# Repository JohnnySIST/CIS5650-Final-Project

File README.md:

# CIS5650-Final-Project : Walk on Stars for Interactive PCB Simulation

# Overview

[LIVE DEMO](https://johnnysist.github.io/CIS5650-Final-Project/)

We are team **Circuit Nova** : [Oliver Hendrych](https://github.com/hendrych-upenn), [Lewis Ghrist](https://siwel-cg.github.io/siwel.cg_websiteV1/index.html#home), and [Hongyi Ding](https://johnnyding.com/portfolio). This project is a browser-based, WebGPU thermal simulation tool for PCB design and prototyping, built on the Walk on Stars (WoStr) algorithm. Users can import or draw PCB layouts, set boundary condition types and values, and interactively move components while the heat distribution updates in real time.

# Motivation and Background

Modern electronics are limited by heat dissipation. Being able to quickly visualize and simulate heat diffusion on PCBs is critical during early prototyping, yet most PCB design tools provide little to no thermal feedback while adjusting layouts. Full finite-element solvers are accurate but slow and don't allow for layout adjustments. Doing a global, high-fidelity solve is also often overkill and requires a full re-simulation every time a small change is made. This project targets that bottleneck by introducing a browser-based GPU thermal estimator built on the Walk-on-Stars (WoStr) algorithm. WoStr allows for fast re-simulation on geometry changes, localized solves over targeted regions, and a progressive convergence that provides immediate, intermediate estimates. All of these are advantageous for quick design iteration and prototyping.

## Current Open Source Availability

Current open source options are limited and take a large number of processing steps before achieving a final result [1]. Users are forced to download many distinct pieces of software for each part of the process, beyond the initial KiCad development, if they want to continue license-free [2]. KiCad boards are exported first to Salome to perform mesh building and conversion. Then, that output is exported ElmerVTK where the FEM simulation is run. Finally, to produce high quality images, that output must be exported to Paraview. If one wants to iterate on their design, then go back to KiCad, modify the appropriate geometry, then complete this whole process again. In our software, the last 3 steps will be condensed to a single software, which will also allow for interative editing to shorten the design loop

## Walk on Spheres & Walk on Stars

Walk on Spheres works by launching random walks from query points until they hit a boundary. Drawing inspiration from path tracing and sphere tracing, each walk contributes to a Monte Carlo estimator that converges toward the true solution of the steady-state heat equation. Because each walk is independent, the method is embarrassingly parallel, making it a perfect fit for WebGPU compute shaders.

Walk on Stars is an extension to the WoS algorithm to allow for a combination of Dirichlet and Neumann boundary conditions, a feature that is needed for physically based heat simulations. The structure is the same in that it is a Monte Carlo based method using random walks from a set of query points. The radius of the sphere used for sphere tracing is only dependent on the Dirichlet boundaries. When walking to the uniformly sampled point on this sphere, if we cross a Neumann boundary, we reflect our walk about the boundary's flux direction and adjust values based on that flux. The walks continue on, only terminating when we finally hit a Dirichlet boundary. This allows for accurate sinks and sources. Again we can take advantage of GPU parallelization to make this process extremely fast.

The original papers, as well as many extentions, can be found here: [https://rohan-sawhney.github.io/mcgp-resources/](https://rohan-sawhney.github.io/mcgp-resources/)

| Walk on Spheres (Dirichlet only)  | Walk on Stars (Dirichlet + Neumann) |
| :-------------------------------: | :---------------------------------: |
|  |    |

# Break Down

The general pipeline involves two main compute shaders. First, we do an initial screening of our simulation domain to get just the query points within the boundaries of our geometry. This can be done once before the simulation starts and allows us to only simulate on point's that will actually result in meaning full data. These query points are then shipped to the second compute shader where the real work happens. This second compute shader handles the actuall simulation. For each query point, we send out these random walks, stepping based on the closest distance to a boundary. This closest distance is found using a BVH struture (or in this case BAH structure since we are in 2D), which drastically speeds up walk times, especially in complex boards. As explained in the WoStr method, at Neumann boundaries, this walk get reflected, picking up some flux value, and at Dirichlet boundarie's, the walk ends and returns the Dirichlet boundary value along with any accumulated flux along the walk. These results then get sent to a final fragment shader, which averages all the walk results for each query point, fits that value through a simple color ramp, and draws it to the screen along with the boundary geometry.

## Interactivity

Here is the layout of the UI:

Major features include:

- Import and export as KiCad PCB formats
- Simulation zone selection
- Change simulation resolution
- Geometry selection, addition/deletion and alteration
- Change boundary conditions and values
- Selection of board layers
- Zooming, panning camera controls
- Toggle simulation on/off
- Live FPS display

A unique advantage of this WoStr method, is that because it is based only on a set of initial query points, we don't need to do a global solve to get results. To take advantage of this, we implemented a simulation zone selection feature that lets users focus computation on a specific region of interest. For complex boards, or if there is a specific area you are particularly interested in, you can easily simulate just on that area in a higher resolution, without paying for the cost of simulating the entire board.

The main user interaction feature is being able to select, add/delete, and move geometry as well as change the boundary types and values as needed. This allows for custom board creation or user imported boards to be edited and adjusted. The final configuration can then be exported out.

The user can also choose which layer of the board they would like to modify and simulate. Modern PCB designs contain many layers, and it is important to be able to simulate any of them. Below is an example of this with the KiCad `kit-dev-coldfire-xilinx_5213` demo project:

|                 FCu Layer                  |                  In1Cu Layer                   |                  In2Cu Layer                   |
| :----------------------------------------: | :--------------------------------------------: | :--------------------------------------------: |
|  |  |  |

Finally, for some quality of life features, we implemented a basic camera system for navigating the board, a live FPS display for performance monitoring, a pause button for the simulation, and a selection menu for adjusting simulation resolution.

Here is a demo video of the tool in action.

## KiCad Integration

An important part of open source development is integrating with other tools from the ecosystem. KiCad is a very popular open source EDA (electronic design automation) tool that is used for PCB design and prototyping. Additionally, other software have capabilities to import and export KiCad PCB files, making it a common element for PCB design. As such, we chose it as our primary integration point, for both import and export of board geometry. Our tool uses a [forked](https://github.com/hendrych-upenn/kicadts) version of the [kicadts](https://github.com/tscircuit/kicadts) package to parse `.kicad_pcb` files and reexport the modified `.kicad_pcb` file. Its plaintext format makes it easy to parse and modify. Upon importing a KiCad PCB file, the tool will parse the file and extract the footprint and segment geometries, which can then be used in the simulation. The user can then modify, delete, or add geometry as needed. When the user is done, the geometry can be exported back to a KiCad PCB file.

# Future Work

There are still some additional features that can be added for more functionality or better resutls. For starters, there has been a lot of recent work on extending or improving the Walk on Stars algorithm. This includes things like faster convergence and more complex boundary types. The simulation at the moment doesn't take into account material properties, which in a full, physically accurate simulation is important. As a prototying tool, getting this approximate solution is still valuable, but WoStr can be extended to support materal properties. Additionally, the pipeline can be extended to support more geometry types beyond simple segments and circles, making it more in line with prexisting PCB editors. Finally, as always, further optimizations and performance improvemnts can be made for smoother and faster results.

# References

1: [https://jrainimo.com/build/2024/11/oss-thermal-simulation-of-pcbs/](https://jrainimo.com/build/2024/11/oss-thermal-simulation-of-pcbs/)

2: [https://resources.altium.com/p/why-you-should-use-thermal-prototyping-instead-simulations](https://resources.altium.com/p/why-you-should-use-thermal-prototyping-instead-simulations)

3: [https://jacco.ompf2.com/2022/04/13/how-to-build-a-bvh-part-1-basics/](https://jacco.ompf2.com/2022/04/13/how-to-build-a-bvh-part-1-basics/)

4: [https://rohan-sawhney.github.io/mcgp-resources/](https://rohan-sawhney.github.io/mcgp-resources/)

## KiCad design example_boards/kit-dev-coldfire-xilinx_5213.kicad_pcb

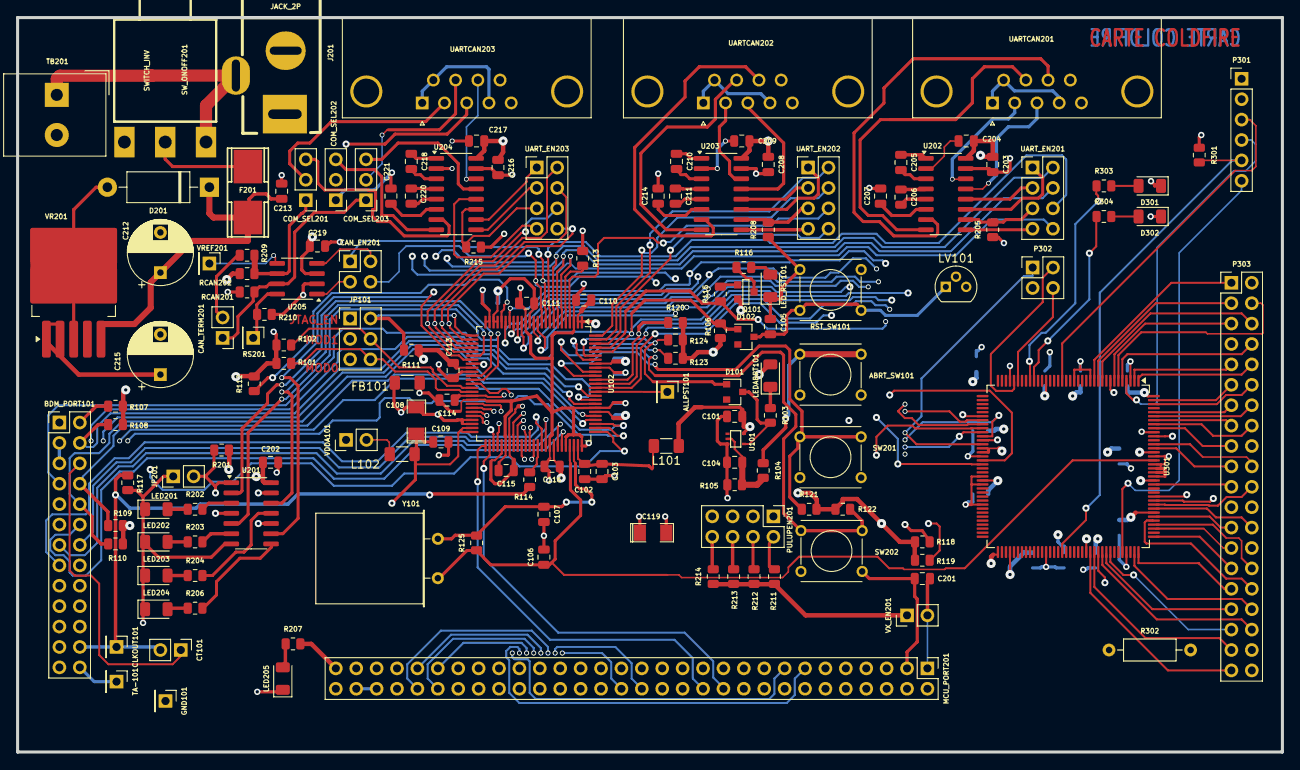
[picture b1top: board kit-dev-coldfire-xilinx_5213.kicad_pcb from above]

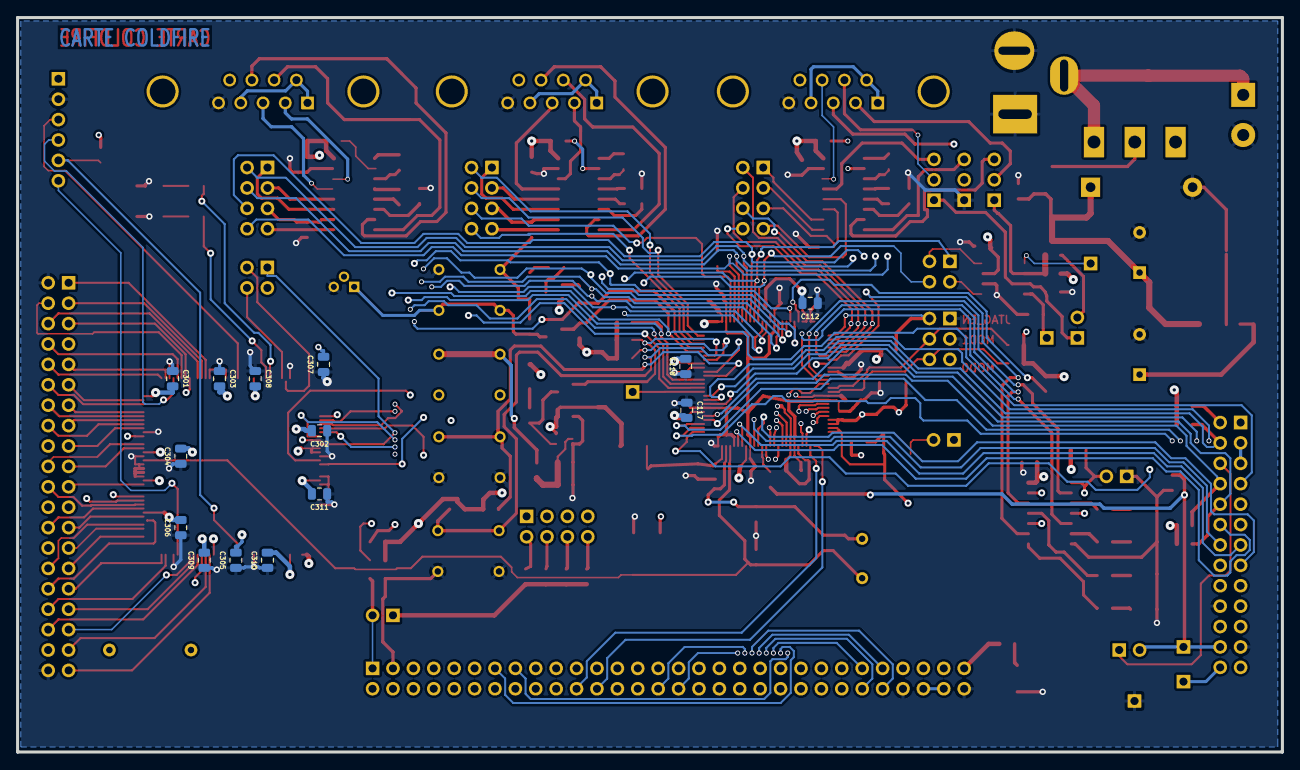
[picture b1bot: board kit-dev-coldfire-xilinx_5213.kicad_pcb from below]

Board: 4 copper layers, 157.5 x 91.4 mm, 160 parts (14 on the bottom side), 209 nets.

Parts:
ABRT_SW101: SW_PUSH; SW_PUSH_SMALL
ALLPST101: CONN_1; PinHeader_1x01_P2.54mm_Vertical
BDM_PORT101: CONN_13X2; PinHeader_2x13_P2.54mm_Vertical
C101, C103, C104, C109, C110, C111, C112, C113, C114, C115, C116, C117, C118, C201, C202, C203, C204, C205, C206, C207, C208, C209, C210, C211, C213, C214, C216, C217, C218, C219, C220, C221, C301, C302, C303, C304, C305, C306, C307, C308, C309, C310, C311: 100nF; C_0805_2012Metric
C102, C105: 1nF; C_0805_2012Metric
C106, C107: 10pF; C_0805_2012Metric
C108: 10uF; SM1206POL
C119: 100uF; SM1206POL
C212: 10uF; CP_Radial_D8.0mm_P5.00mm
C215: 220uF; CP_Radial_D8.0mm_P5.00mm
CAN_EN201: CONN_2X2; PinHeader_2x02_P2.54mm_Vertical
CAN_TERM201: JUMPER; PinHeader_1x02_P2.54mm_Vertical
CLKOUT101: CONN_1; PinHeader_1x01_P2.54mm_Vertical
COM_SEL201, COM_SEL202, COM_SEL203: CONN_3; PinHeader_1x03_P2.54mm_Vertical
CT101: JUMPER; PinHeader_1x02_P2.54mm_Vertical
D101, D102: BAT54; D_SOT-23_ANK
D201: 1N4004; D_DO-15_P12.70mm_Horizontal
D301, D302: LED; LED_1206_3216Metric
F201: FUSE; FSUPCMS
FB101: BEAD; R_1206_3216Metric_Pad1.30x1.75mm_HandSolder
GND101: CONN_1; PinHeader_1x01_P2.54mm_Vertical
J201: JACK_2P; JACK_ALIM
JP101: JUMPER_TRIPLE; PinHeader_2x03_P2.54mm_Vertical
JP201: JUMPER; PinHeader_1x02_P2.54mm_Vertical
L101, L102: 10uH; R_1206_3216Metric_Pad1.30x1.75mm_HandSolder
LED201, LED202, LED203, LED204, LED205: LED; LED_1206_3216Metric
LEDABRT101: LED_RED; LED_1206_3216Metric
LED_RST101: LED_RED; LED_1206_3216Metric
LV101: DS1818; TO-92
MCU_PORT201: CONN_30X2; PinHeader_2x30_P2.54mm_Vertical
P301: CONN_6; PinHeader_1x06_P2.54mm_Vertical
P302: CONN_2X2; PinHeader_2x02_P2.54mm_Vertical
P303: CONN_20X2; PinHeader_2x20_P2.54mm_Vertical
PULUPEN201: CONN_4X2; PinHeader_2x04_P2.54mm_Vertical
Q101: 3906; SOT23EBC
R101, R102, R106, R107, R108, R109, R110, R111, R112, R211, R212, R213, R214: 4,7K; R_0805_2012Metric
R103, R116, R202, R203, R204, R206, R207: 270; R_0805_2012Metric
R104, R210, R303, R304: 1K; R_0805_2012Metric
R105: 20K; R_0805_2012Metric
R113: 0; R_0805_2012Metric
R114: 22; R_0805_2012Metric
R115: 4.7K; R_0805_2012Metric
R117, R118, R119, R120, R121, R122, R123, R124, R201, R205, R208, R215: 10K; R_0805_2012Metric
R125: 1M; R_0805_2012Metric
R209: 62; R_0805_2012Metric
R301: 4K7; R_0805_2012Metric
R302: 3,3; R_Axial_DIN0207_L6.3mm_D2.5mm_P10.16mm_Horizontal
RCAN201, RCAN202: R; R_0805_2012Metric
RS201: CONN_1; PinHeader_1x01_P2.54mm_Vertical
RST_SW101: SW_PUSH; SW_PUSH_SMALL
SW201, SW202: SW_PUSH; SW_PUSH_SMALL
SW_ONOFF201: SWITCH_INV; SW_SPDT
TA-101: CONN_1; PinHeader_1x01_P2.54mm_Vertical
TB201: CONN_2; Altech_AK300_1x02_P5.00mm_45-Degree
U101: 74AHC1G14; SOT353
U102: MCF5213-LQFP100; LQFP-100_14x14mm_P0.5mm
U201: 74HC125; SOIC-14_3.9x8.7mm_P1.27mm
U202, U203, U204: MAX202; SOIC-16_3.9x9.9mm_P1.27mm
U205: PCA82C251; SOIC-8_3.9x4.9mm_P1.27mm
U301: XCR3256-TQ144; TQFP-144_20x20mm_P0.5mm
UARTCAN201, UARTCAN202, UARTCAN203: DB9; DSUB-9_Female_Horizontal_P2.77x2.84mm_EdgePinOffset7.70mm_H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
UART_EN201, UART_EN202, UART_EN203: CONN_4X2; PinHeader_2x04_P2.54mm_Vertical
VDDA101: JUMPER; PinHeader_1x02_P2.54mm_Vertical
VR201: LT1129_QPACK; TO-263-5_TabPin3
VREF201: CONN_1; PinHeader_1x01_P2.54mm_Vertical
VX_EN201: JUMPER; PinHeader_1x02_P2.54mm_Vertical
Y101: 8MHz; Crystal_HC18-U_Horizontal

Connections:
+3.3V: ABRT_SW101.2, BDM_PORT101.9, BDM_PORT101.25 (P24), C101.2, C110.1, C111.1, C112.1, C113.1, C114.1, C115.1, C116.1, C117.1, C118.1, C119.1, C202.1, C203.1, C204.1, C208.1, C209.1, C215.1, C216.1, C217.1, C219.1, C301.1, C302.1, C303.1, C304.1, C305.1, C306.1, C307.1, C308.1, C309.1, C310.1, C311.1, L101.1, LEDABRT101.2 (A), LV101.2 (In), MCU_PORT201.59, P301.1, Q101.1 (E), R101.1, R102.1, R106.1, R107.1, R108.1, R109.1, R110.1, R111.1, R112.2, R118.2, R119.2, R120.2, R121.2, R122.2, R123.2, R124.2, R201.1, R207.2, R211.1, R212.1, R213.1, R214.1, R301.1, R302.1, RCAN202.1, U101.5 (VCC), U102.1 (VCC), U102.2 (VCC), U102.14 (VCC), U102.22 (VCC), U102.23 (VCC), U102.34 (VCC), U102.41 (VCC), U102.55 (VSTBY), U102.57 (VCC), U102.68 (VCC), U102.81 (VCC), U102.93 (VCC), U201.14 (VCC), U202.16 (VCC), U203.16 (VCC), U204.16 (VCC), U205.3 (VCC), U301.24 (VCC), U301.50 (VCC), U301.51 (VCC), U301.58 (VCC), U301.73 (VCC), U301.76 (VCC), U301.95 (VCC), U301.115 (VCC), U301.123 (VCC), U301.130 (VCC), U301.144 (VCC), VDDA101.1, VR201.1 (OUT), VR201.2 (SENSE), VX_EN201.1
/ALLPST: ALLPST101.1, U102.86 (ALLPST)
/AN0: MCU_PORT201.10, U102.43 (AN0/PAN0)
/AN1: MCU_PORT201.12, U102.44 (AN1/PAN1)
/AN2: MCU_PORT201.14, U102.45 (AN2/PAN2)
/AN3: MCU_PORT201.16, U102.46 (AN3/PAN3)
/AN4: MCU_PORT201.18, U102.54 (AN4/PAN4)
/AN5: MCU_PORT201.20, U102.53 (AN5/PAN5)
/AN6: MCU_PORT201.22, U102.52 (AN6/PAN6)
/AN7: MCU_PORT201.24, U102.51 (AN7/PAN7)
/BKPT-: BDM_PORT101.2, R107.2, U102.76 (~BKPT/TMS)
/CANRX: CAN_EN201.4, MCU_PORT201.28, PULUPEN201.7, U102.11 (SDA/CANRX/PAS1/URXD2)
/CANTX: CAN_EN201.1, MCU_PORT201.26, PULUPEN201.5, U102.10 (SCL/CANTX/PAS0/UTXD2)
/CLKIN/EXTAL: C107.1, R125.2, U102.73 (CLKIN/EXTAL), Y101.1
/CLKMOD0: JP101.6, R101.2, U102.40 (CLKMOD0)
/CLKMOD1: JP101.4, R102.2, U102.39 (CLKMOD1)
/DDAT0: BDM_PORT101.19, U102.77 (DDATA0/PDD4)
/DDAT1: BDM_PORT101.18, U102.78 (DDATA1/PDD5)
/DDAT2: BDM_PORT101.17, U102.83 (DDATA2/PDD6)
/DDAT3: BDM_PORT101.16, U102.84 (DDATA3/PDD7)
/DSCLK: BDM_PORT101.4, R108.2, U102.85 (DSCLK/~TRST)
/DSI: BDM_PORT101.8, R109.2, U102.79 (DSI/TDI)
/DSO: BDM_PORT101.10, R110.2, U102.80 (DSO/TDO)
/DSPI_DOUT: MCU_PORT201.17, U102.17 (QSPI_DOUT/EZPQ/CANTX/RXD0/PQS0), U301.47 (M12)
/DTIN0: MCU_PORT201.34, U102.36 (DTIN0/DTOUT0/PWM0/PTC0), U201.2 (D)
/DTIN1: MCU_PORT201.36, U102.37 (DTIN1/DTOUT1/PWM2/PTC1), U201.5 (D)
/DTIN2: MCU_PORT201.38, U102.31 (DTIN2/DTOUT2/PWM4/PTC2), U201.12 (D)
/DTIN3: MCU_PORT201.40, U102.32 (DTIN3/DTOUT3/PWM6/PTC3), U201.9 (D)
/GPT0: MCU_PORT201.49, U102.58 (GPT0/PWM1/PTA0)
/GPT1: MCU_PORT201.50, U102.59 (GPT1/PWM3/PTA1)
/GPT2: MCU_PORT201.51, U102.61 (GPT2PWM5//PTA2)
/GPT3: MCU_PORT201.52, U102.62 (GPT3/PWM7/PTA3)
/IRQ-1: MCU_PORT201.2, R118.1, U102.87 (~IRQ1/PNQ1/SYNCA/PWM1), U301.42 (O2)
/IRQ-2: MCU_PORT201.8, R119.1, U102.88 (~IRQ2/PNQ2), U301.43 (O1)
/IRQ-3: MCU_PORT201.31, R120.1, U102.89 (~IRQ3/PNQ3), U301.44 (O0)
/IRQ-4: MCU_PORT201.33, R121.1, SW201.1, U102.90 (~IRQ4/PNQ4)
/IRQ-5: MCU_PORT201.35, R122.1, SW202.1, U102.91 (~IRQ5/PNQ5)
/IRQ-6: MCU_PORT201.37, R123.1, U102.94 (~IRQ6/PNQ6)
/IRQ-7: D101.2 (A), MCU_PORT201.39, R124.1, U102.95 (~IRQ7/PNQ7)
/JTAG_EN: JP101.2, R111.2, U102.26 (JTAG_EN)
/PST0: BDM_PORT101.15, U102.65 (PST0/PDD0)
/PST1: BDM_PORT101.14, U102.66 (PST1/PDD1)
/PST2: BDM_PORT101.13, U102.69 (PST2/PDD2)
/PST3: BDM_PORT101.12, U102.70 (PST3/PDD3)
/PWM1: MCU_PORT201.13, U102.38 (PWM1/PTD0)
/PWM3: MCU_PORT201.15, U102.33 (PWM3/PTD1)
/PWM5: MCU_PORT201.30, U102.60 (PWM5/PTD2)
/PWM7: MCU_PORT201.32, U102.63 (PWM7/PTD3)
/QSPI_CLK: MCU_PORT201.21, PULUPEN201.1, U102.18 (QSPI_CLK/EZPCK/SCL/RTS1/PQS2), U301.48 (M11)
/QSPI_CS0: MCU_PORT201.23, PULUPEN201.3, U102.20 (QSPI_CS0/SDA/CTS1/PQS3)
/QSPI_CS1: MCU_PORT201.25, U102.19 (QSPI_CS1/PQS4), U301.54 (M1)
/QSPI_CS2: MCU_PORT201.27, U102.13 (QSPI_CS2/PQS5), U301.45 (M15)
/QSPI_CS3: MCU_PORT201.29, U102.12 (QSPI_CS3/SYNCA/SYNCB/PQS6)
/QSPI_DIN: MCU_PORT201.19, U102.16 (QSPI_DIN/EZPD/CANRX/RXD1/PQS1), U301.46 (M13)
/RCON-: MCU_PORT201.53, R112.1, U102.21 (RCON/EZPCS)
/RSTI-: BDM_PORT101.7, D102.2 (A), MCU_PORT201.6, R106.2, U102.96 (RSTI)
/RSTO-: MCU_PORT201.4, R115.1, U102.97 (RSTO)
/TCLK: BDM_PORT101.24 (P20), CLKOUT101.1, CT101.2, R114.2, R117.1
/UCTS0: MCU_PORT201.44, U102.6 (~UCTS0/CANRX/PUA3), UART_EN201.8
/UCTS1: MCU_PORT201.11, P302.1, U102.98 (~UCTS1/SYNCA/URXD2/PUB3), U301.49 (M4), UART_EN202.8
/UCTS2: MCU_PORT201.48, U102.27 (~UCTS2/PUC3), UART_EN203.8
/URTS0: MCU_PORT201.42, U102.9 (~URTS0/CANTX/PUA2), UART_EN201.6
/URTS1: MCU_PORT201.9, P302.3, U102.4 (~URTS1/SYNCB/UTXD2/PUB2), U301.53 (M2), UART_EN202.6
/URTS2: MCU_PORT201.46, U102.30 (~URTS2/PUC2), UART_EN203.6
/URXD0: MCU_PORT201.43, U102.7 (URXD0/PUA1), UART_EN201.4
/URXD1: MCU_PORT201.7, U102.100 (URXD1/PUB1), UART_EN202.4
/URXD2: MCU_PORT201.47, U102.28 (URXD2/PUC1), UART_EN203.4
/UTXD0: MCU_PORT201.41, U102.8 (UTXD0/PUA0), UART_EN201.2
/UTXD1: MCU_PORT201.5, U102.99 (UTXD1/PUB0), UART_EN202.2
/UTXD2: MCU_PORT201.45, U102.29 (UTXD2/PUC0), UART_EN203.2
/VCCA: C108.1, C109.1, L102.2, MCU_PORT201.55, MCU_PORT201.57, U102.49 (VRH), U102.50 (VCCA)
/VDDPLL: C102.1, C103.1, L101.2, U102.74 (VCCPLL)
/XTAL: C106.1, R125.1, U102.72 (XTAL), U301.128 (CLK0/IN0), Y101.2
/inout_user/CAN_H: CAN_TERM201.1, COM_SEL203.1, RCAN201.2, U205.7 (CAN+)
/inout_user/CAN_L: COM_SEL201.1, R209.1, RCAN202.2, U205.6 (CAN-)
/inout_user/CTS0: U202.8 (R2IN), UARTCAN201.7
/inout_user/CTS1: U203.8 (R2IN), UARTCAN202.7
/inout_user/CTS2/CANH: COM_SEL203.2 (PM), UARTCAN203.7
/inout_user/RTS0: U202.7 (T2OUT), UARTCAN201.8
/inout_user/RTS1: U203.7 (T2OUT), UARTCAN202.8
/inout_user/RTS2: U204.14 (T1OUT), UARTCAN203.8
/inout_user/RXD0: U202.13 (R1IN), UARTCAN201.3
/inout_user/RXD1: U203.13 (R1IN), UARTCAN202.3
/inout_user/RXD2: COM_SEL202.2 (PM), UARTCAN203.3
/inout_user/RxD_CAN: CAN_EN201.2, U205.4 (RxD)
/inout_user/TXD0: U202.14 (T1OUT), UARTCAN201.2
/inout_user/TXD1: U203.14 (T1OUT), UARTCAN202.2
/inout_user/TXD2/CANL: COM_SEL201.2 (PM), UARTCAN203.2
/inout_user/TxD_CAN: CAN_EN201.3, U205.1 (TxD)
/xilinx/+3,3V_OUT: P303.38, R302.2
/xilinx/LED_TEST1: R303.1, U301.28 (N15)
/xilinx/LED_TEST2: R304.1, U301.27 (N14)
/xilinx/TCK: P301.5, R301.2, U301.89 (E0/TCK)
/xilinx/TDI: P301.4, U301.4 (J0/TDI)
/xilinx/TDO: P301.6, U301.104 (A2/TDO)
/xilinx/TMS: P301.3, U301.20 (N0/TMS)
/xilinx/XIL_D0: P303.1, U301.12 (L2)
/xilinx/XIL_D1: P303.3, U301.11 (J15)
/xilinx/XIL_D2: P303.5, U301.7 (J4)
/xilinx/XIL_D3: P303.7, U301.8 (J11)
/xilinx/XIL_D4: P303.9, U301.2 (I0)
/xilinx/XIL_D5: P303.11, U301.143 (I4)
/xilinx/XIL_D6: P303.13, U301.140 (I14)
/xilinx/XIL_D7: P303.15, U301.138 (K2)
/xilinx/XIL_D8: P303.17, U301.136 (K11)
/xilinx/XIL_D9: P303.19, U301.131 (K15)
/xilinx/XIL_D10: P303.21, U301.122 (D15)
/xilinx/XIL_D11: P303.23, U301.119 (D11)
/xilinx/XIL_D12: P303.25, U301.114 (D0)
/xilinx/XIL_D13: P303.27, U301.111 (B12)
/xilinx/XIL_D14: P303.29, U301.109 (B4)
/xilinx/XIL_D15: P303.31, U301.108 (B1)
/xilinx/XIL_D16: P303.33, U301.100 (A12)
/xilinx/XIL_D17: P303.35, U301.101 (A11)
/xilinx/XIL_D18: P303.37, U301.97 (C1)
/xilinx/XIL_D19: P303.39, U301.96 (C2)
/xilinx/XIL_D20: P303.4, U301.6 (J3)
/xilinx/XIL_D21: P303.6, U301.10 (J14)
/xilinx/XIL_D22: P303.8, U301.5 (J2)
/xilinx/XIL_D23: P303.10, U301.1 (I1)
/xilinx/XIL_D24: P303.12, U301.142 (I12)
/xilinx/XIL_D25: P303.14, U301.139 (I15)
/xilinx/XIL_D26: P303.16, U301.137 (K4)
/xilinx/XIL_D27: P303.18, U301.134 (K12)
/xilinx/XIL_D28: P303.20, U301.132 (K14)
/xilinx/XIL_D29: P303.22, U301.117 (D2)
/xilinx/XIL_D30: P303.24, U301.118 (D4)
/xilinx/XIL_D31: P303.26, U301.116 (D1)
/xilinx/XIL_D32: P303.28, U301.98 (C0)
/xilinx/XIL_D33: P303.30, U301.112 (B14)
/xilinx/XIL_D34: P303.32, U301.113 (B15)
/xilinx/XIL_D35: P303.34, U301.107 (B0)
/xilinx/XIL_D36: P303.36, U301.99 (A13)
GND: BDM_PORT101.3, BDM_PORT101.5, BDM_PORT101.11, BDM_PORT101.20, BDM_PORT101.23, C101.1, C102.2, C103.2, C104.2, C105.2, C106.2, C107.2, C110.2, C111.2, C112.2, C113.2, C114.2, C115.2, C116.2, C117.2, C118.2, C119.2, C201.1, C202.2, C203.2, C207.2, C208.2, C212.2, C213.2, C214.2, C215.2, C216.2, C219.2, C221.2, C301.2, C302.2, C303.2, C304.2, C305.2, C306.2, C307.2, C308.2, C309.2, C310.2, C311.2, COM_SEL202.1, D201.2 (A), D301.1 (K), D302.1 (K), FB101.1, GND101.1, J201.1, J201.2, JP101.1, JP101.3, JP101.5, JP201.1, LED201.1 (K), LED202.1 (K), LED203.1 (K), LED204.1 (K), LED205.1 (K), LED_RST101.1 (K), LV101.3 (Gbd), MCU_PORT201.3, MCU_PORT201.54, MCU_PORT201.60, P301.2, P303.2, P303.40, R105.2, R113.2, R117.2, R205.1, R208.1, R210.2, R215.1, RCAN201.1, RST_SW101.2, SW201.2, SW202.2, TB201.2 (PM), U101.3 (GND), U102.3 (GND), U102.15 (GND), U102.24 (GND), U102.25 (GND), U102.35 (GND), U102.42 (GND), U102.56 (GND), U102.67 (GND), U102.71 (GNDPLL), U102.75 (GND), U102.82 (GND), U102.92 (GND), U201.7 (GND), U202.15 (GND), U203.15 (GND), U204.15 (GND), U205.2 (GND), U301.3 (GND), U301.13 (PORT_EN), U301.17 (GND), U301.33 (GND), U301.52 (GND), U301.57 (GND), U301.59 (GND), U301.64 (GND), U301.85 (GND), U301.105 (GND), U301.124 (GND), U301.125 (CLK3/IN3), U301.126 (CLK2/IN2), U301.127 (CLK1/IN1), U301.129 (GND), U301.135 (GND), UARTCAN201.5, UARTCAN202.5, UARTCAN203.5, VR201.3 (GND)
GNDA: C108.2, C109.2, FB101.2, MCU_PORT201.56, MCU_PORT201.58, U102.47 (VSSA), U102.48 (VRL)
unnamed: ABRT_SW101.1, R104.1
unnamed: BDM_PORT101.6, CT101.1
unnamed: BDM_PORT101.26 (P22), TA-101.1
unnamed: C104.1, R104.2, R105.1, U101.2
unnamed: CAN_TERM201.2, R209.2
unnamed: COM_SEL201.3, U204.7 (T2OUT)
unnamed: COM_SEL202.3, U204.8 (R2IN)
unnamed: COM_SEL203.3, U204.13 (R1IN)
unnamed: D101.1 (K), R103.2, U101.4
unnamed: C105.1, D102.1 (K), LV101.1 (Rst), RST_SW101.1
unnamed: C212.1, C213.1, D201.1 (K), F201.2, VR201.5 (IN)
unnamed: D301.2 (A), R303.2
unnamed: D302.2 (A), R304.2
unnamed: F201.1, SW_ONOFF201.2
unnamed: L102.1, VDDA101.2
unnamed: LED201.2 (A), R202.1
unnamed: LED202.2 (A), R203.1
unnamed: LED203.2 (A), R204.1
unnamed: LED204.2 (A), R206.1
unnamed: LED205.2 (A), R207.1
unnamed: LEDABRT101.1 (K), R103.1
unnamed: LED_RST101.2 (A), R116.2
unnamed: C201.2, MCU_PORT201.1, VX_EN201.2
unnamed: PULUPEN201.2, R211.2
unnamed: PULUPEN201.4, R212.2
unnamed: PULUPEN201.6, R213.2
unnamed: PULUPEN201.8, R214.2
unnamed: Q101.2 (B), R115.2
unnamed: Q101.3 (C), R116.1
unnamed: J201.3, SW_ONOFF201.3, TB201.1
unnamed: R114.1, U102.64 (TCLK/PSTCLK/CLKOUT)
unnamed: R113.1, U102.5 (TEST)
unnamed: JP201.2, R201.2, U201.1 (E), U201.4 (E), U201.10 (E), U201.13 (E)
unnamed: R202.2, U201.3 (O)
unnamed: R203.2, U201.6 (O)
unnamed: R206.2, U201.8 (O)
unnamed: R204.2, U201.11 (O)
unnamed: C205.1, U202.1 (C1+)
unnamed: C205.2, U202.3 (C1-)
unnamed: C206.1, U202.4 (C2+)
unnamed: C206.2, U202.5 (C2-)
unnamed: U202.12 (R1OUT), UART_EN201.3
unnamed: U202.9 (R2OUT), UART_EN201.7
unnamed: U202.11 (T1IN), UART_EN201.1
unnamed: R205.2, U202.10 (T2IN), UART_EN201.5
unnamed: C204.2, U202.2 (V+)
unnamed: C207.1, U202.6 (V-)
unnamed: C210.1, U203.1 (C1+)
unnamed: C210.2, U203.3 (C1-)
unnamed: C211.1, U203.4 (C2+)
unnamed: C211.2, U203.5 (C2-)
unnamed: U203.12 (R1OUT), UART_EN202.3
unnamed: U203.9 (R2OUT), UART_EN202.7
unnamed: U203.11 (T1IN), UART_EN202.1
unnamed: R208.2, U203.10 (T2IN), UART_EN202.5
unnamed: C209.2, U203.2 (V+)
unnamed: C214.1, U203.6 (V-)
unnamed: C218.1, U204.1 (C1+)
unnamed: C218.2, U204.3 (C1-)
unnamed: C220.1, U204.4 (C2+)
unnamed: C220.2, U204.5 (C2-)
unnamed: U204.12 (R1OUT), UART_EN203.7
unnamed: U204.9 (R2OUT), UART_EN203.3
unnamed: R215.2, U204.11 (T1IN), UART_EN203.5
unnamed: U204.10 (T2IN), UART_EN203.1
unnamed: C217.2, U204.2 (V+)
unnamed: C221.1, U204.6 (V-)
unnamed: R210.1, RS201.1, U205.8 (Rsl)
unnamed: U205.5 (Vref), VREF201.1
unnamed: P302.4, U301.31 (P4)
unnamed: P302.2, U301.32 (P11)
unnamed: UARTCAN201.1, UARTCAN201.4, UARTCAN201.6
unnamed: UARTCAN202.1, UARTCAN202.4, UARTCAN202.6
unnamed: UARTCAN203.1, UARTCAN203.4, UARTCAN203.6

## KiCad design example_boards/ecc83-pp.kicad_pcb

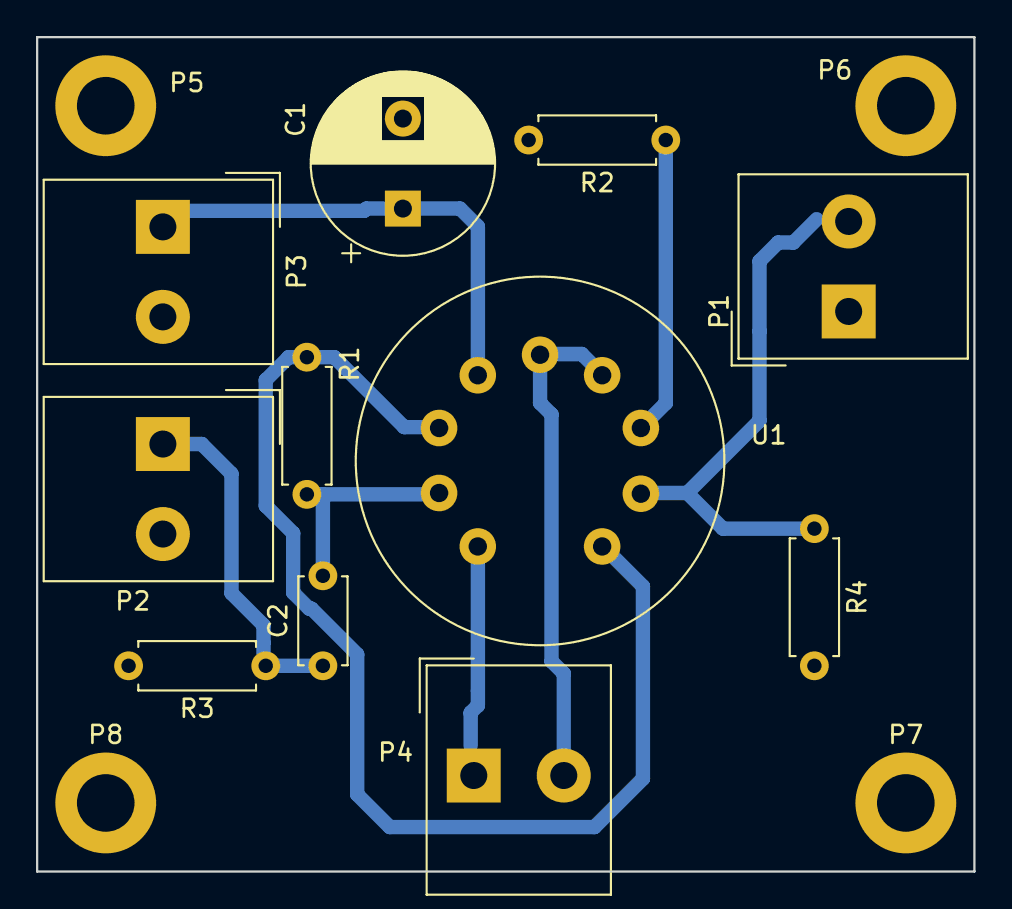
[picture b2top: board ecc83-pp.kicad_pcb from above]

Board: 2 copper layers, 52.1 x 46.4 mm, 15 parts (0 on the bottom side), 9 nets.

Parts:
C1: 10uF; CP_Radial_D10.0mm_P5.00mm
C2: 680nF; C_Disc_D4.7mm_W2.5mm_P5.00mm
P1: IN; Altech_AK300_1x02_P5.00mm_45-Degree
P2: OUT; Altech_AK300_1x02_P5.00mm_45-Degree
P3: POWER; Altech_AK300_1x02_P5.00mm_45-Degree
P4: CONN_2; Altech_AK300_1x02_P5.00mm_45-Degree
P5, P6, P7, P8: MOUNTING_HOLE; MountingHole_3.2mm_M3_DIN965_Pad
R1, R2: 1.5K; R_Axial_DIN0207_L6.3mm_D2.5mm_P7.62mm_Horizontal
R3: 100K; R_Axial_DIN0207_L6.3mm_D2.5mm_P7.62mm_Horizontal
R4: 47K; R_Axial_DIN0207_L6.3mm_D2.5mm_P7.62mm_Horizontal
U1: ECC83; Valve_ECC-83-1

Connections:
GND: C1.2, P1.1, P2.2 (PM), P3.2 (PM), R2.2, R3.2, R4.2
unnamed: P1.2 (PM), R4.1, U1.2 (G)
unnamed: C2.1, P2.1, R3.1
unnamed: C1.1, P3.1, U1.6 (A)
unnamed: P4.1, U1.9 (F2)
unnamed: P4.2 (PM), U1.4 (F1), U1.5 (F1)
unnamed: R1.1, U1.1 (A), U1.7 (G)
unnamed: C2.2, R1.2, U1.8 (K)
unnamed: R2.1, U1.3 (K)

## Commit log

2025-11-11 Hello Triangle rendering
2025-11-11 Basic compute -> frag pipeline setup
2025-11-12 Compute UV to frag texture sample implemented
2025-11-12 basic interactive
2025-11-12 Basic WOS in
2025-11-12 milestone 1 presentation
2025-11-12 HW4 framework. Added Obj loading
2025-11-13 Seperate Rendere and uv preprocess compute
2025-11-14 Started removing texture passing pipeline for f buffers
2025-11-14 Removed texture passing
    Pipeline now uses f32 arrays indexed by uv
2025-11-22 Basic live converging (need to do ping pong buffer?)
2025-11-23 Basic boundary buffer (just circles)
2025-11-24 init kicad importer
2025-11-24 add example board
2025-11-24 get objects on layer
2025-11-24 Basic WoStr setup
2025-11-24 refactor to renderer and no more uv
2025-11-24 Added camera interacions
2025-11-24 add camera manipulation back
2025-11-24 import board v1
2025-11-24 Added camera selection
2025-11-24 Added selection box drawing
2025-11-24 interactive changing sizes
2025-11-24 Milestone 2 video
2025-11-24 readme outline
2025-11-24 add media and some readme
2025-11-24 add milestone 2 presentation
2025-11-25 Added fps badge
2025-12-01 Very basic grid structure in CPU side
2025-12-01 temp combining
2025-12-01 better react
2025-12-01 fork kicadts
2025-12-01 Deploy static site
2025-12-01 MS3: Added sim toggle. Deploy to gh-pages
2025-12-03 Incorrect spacial grid (WIP)
    Replacing this with BVH
2025-12-05 Updated Wostr, buggy BVH
2025-12-06 Better version of WoStr
2025-12-06 Pretty colors
2025-12-06 Parameter changes
2025-12-06 another example board
2025-12-06 Added new test board
2025-12-06 revert custom kicadts for now
2025-12-06 readd ui
2025-12-06 update package list
2025-12-06 renderer and wgsl board bounding changes
2025-12-06 add board bounds and fix buffer alloc
2025-12-06 Slow BVH WoStr
2025-12-06 reset totalwalks on renderer reset
2025-12-06 Double BVH setup
2025-12-06 dynamic board size
2025-12-06 Added Sim On/Off functionality
2025-12-07 wrap only computes in sim enable
2025-12-07 usememo on board constrainst to prevent unnecessary rerenders
2025-12-07 renderer refactor
2025-12-07 better UI
2025-12-07 fix viewres update
2025-12-07 extra renderer destroys
2025-12-07 renderer remove async add alignment
2025-12-07 Updated static page
2025-12-07 increase width of fps badge
2025-12-07 Fixed build errors
2025-12-07 separate out update geometry for renderer
2025-12-07 include rendertypes
2025-12-07 set sim size on board reload
2025-12-07 resolution option
2025-12-07 Updated BVH creation and traversal
2025-12-07 better updating and boundary initials
2025-12-07 selected info on right
2025-12-07 slight typing
2025-12-07 Minor Cleanups
2025-12-07 boundary type selection
2025-12-07 update render bvh to build with global index
2025-12-08 Boundary always showing up
2025-12-08 selection highlighting
2025-12-08 changed colors
2025-12-08 Added insert circle/segment
2025-12-08 dragging
2025-12-08 Images
2025-12-08 Update readme V1
2025-12-08 Update readme v2
2025-12-08 add back adding circle
2025-12-08 readd adding segments
2025-12-08 Added links
2025-12-08 Merged and solved woscanvas conflict
2025-12-08 Boundary drawing bug fix
2025-12-08 select target layer
2025-12-08 color other circles in footprint
2025-12-08 Added auto-selection and deletion
2025-12-08 angle
2025-12-08 Update Readme V3
2025-12-08 update export
2025-12-08 updated readme v2
2025-12-08 Update readme V4
2025-12-08 npm update and use own kicadts
2025-12-08 Added video
2025-12-08 Centered image
2025-12-08 Added README for interactivity
2025-12-08 Update static page (Final Version)
2025-12-08 Minor readme updates 1
2025-12-08 kicad integration in readme
2025-12-08 add line about board layers
2025-12-08 Added more images
2025-12-08 kicad integration video and layers inclusion
2025-12-08 proper readme includes
2025-12-08 rename inner copper files
2025-12-08 Added final presentation
